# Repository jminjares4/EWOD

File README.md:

# **EWOD** :zap:

## **Description**
This repository hold the hardware designed files for EWOD Senior project. The hardware was developed in KiCAD.

## **Table of Contents**
* [3D](https://github.com/jminjares4/EWOD/tree/main/3D)
  * EWOD step file
* [Hardware](https://github.com/jminjares4/EWOD/tree/main/Hardware)
  * [EWOD KiCad](https://github.com/jminjares4/EWOD/tree/main/Hardware/EWOD%20KiCad)
  * [jlcpcb](https://github.com/jminjares4/EWOD/tree/main/Hardware/jlcpcb)
  * [Readme](https://github.com/jminjares4/EWOD/tree/main/Hardware/README.md)
* [Images](https://github.com/jminjares4/EWOD/tree/main/images)
  * EWOD schematic and printed circuit board (PCB)   
* [Readme](https://github.com/jminjares4/EWOD)

## **Requirements**
- [x] Surface mount SPDT Relays
  - [x] Onboard status LEDs 
- [x] Screw terminals
  - [x] AC Power
  - [x] Step-down transformer 
- [x] SPST Power switch
- [x] External UART to flash ESP32 
- [x] Testpoint
  - [x] 3.3V
  - [x] 5V
  - [x] 16V
  - [x] 164V  

## **EWOD PCB**

## **Development**
| **EWOD** | **Hardware/Software**|
| :--- | :--- |
|**Microcontroller**| |
|**Documentation**| |
| **Electronic Design Automation** ||

## **License**

## **Acknowledgements**
* ECE Department (UTEP)

## **Author**
* [**Jesus Minjares**](https://github.com/jminjares4)<br>
  * **Master of Science in Computer Engineering**<br>

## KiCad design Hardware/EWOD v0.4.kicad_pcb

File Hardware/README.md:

# **EWOD Hardware** :zap:
This directory hold the hardware files for EWOD which was developed in KiCad.

## **Table of Contents**
* **EWOD KiCad**
  * EWOD hardware development was done in KiCad
* **jlcpcb**
  * JLCPCB files for assembly and gerber files

## **Schematic**

## **Top Layer**

## **Bottom Layer**

## **Printed Circuit Board**

## **Author**
* [**Jesus Minjares**](https://github.com/jminjares4)<br>
  * **Master of Science in Computer Engineering**<br>

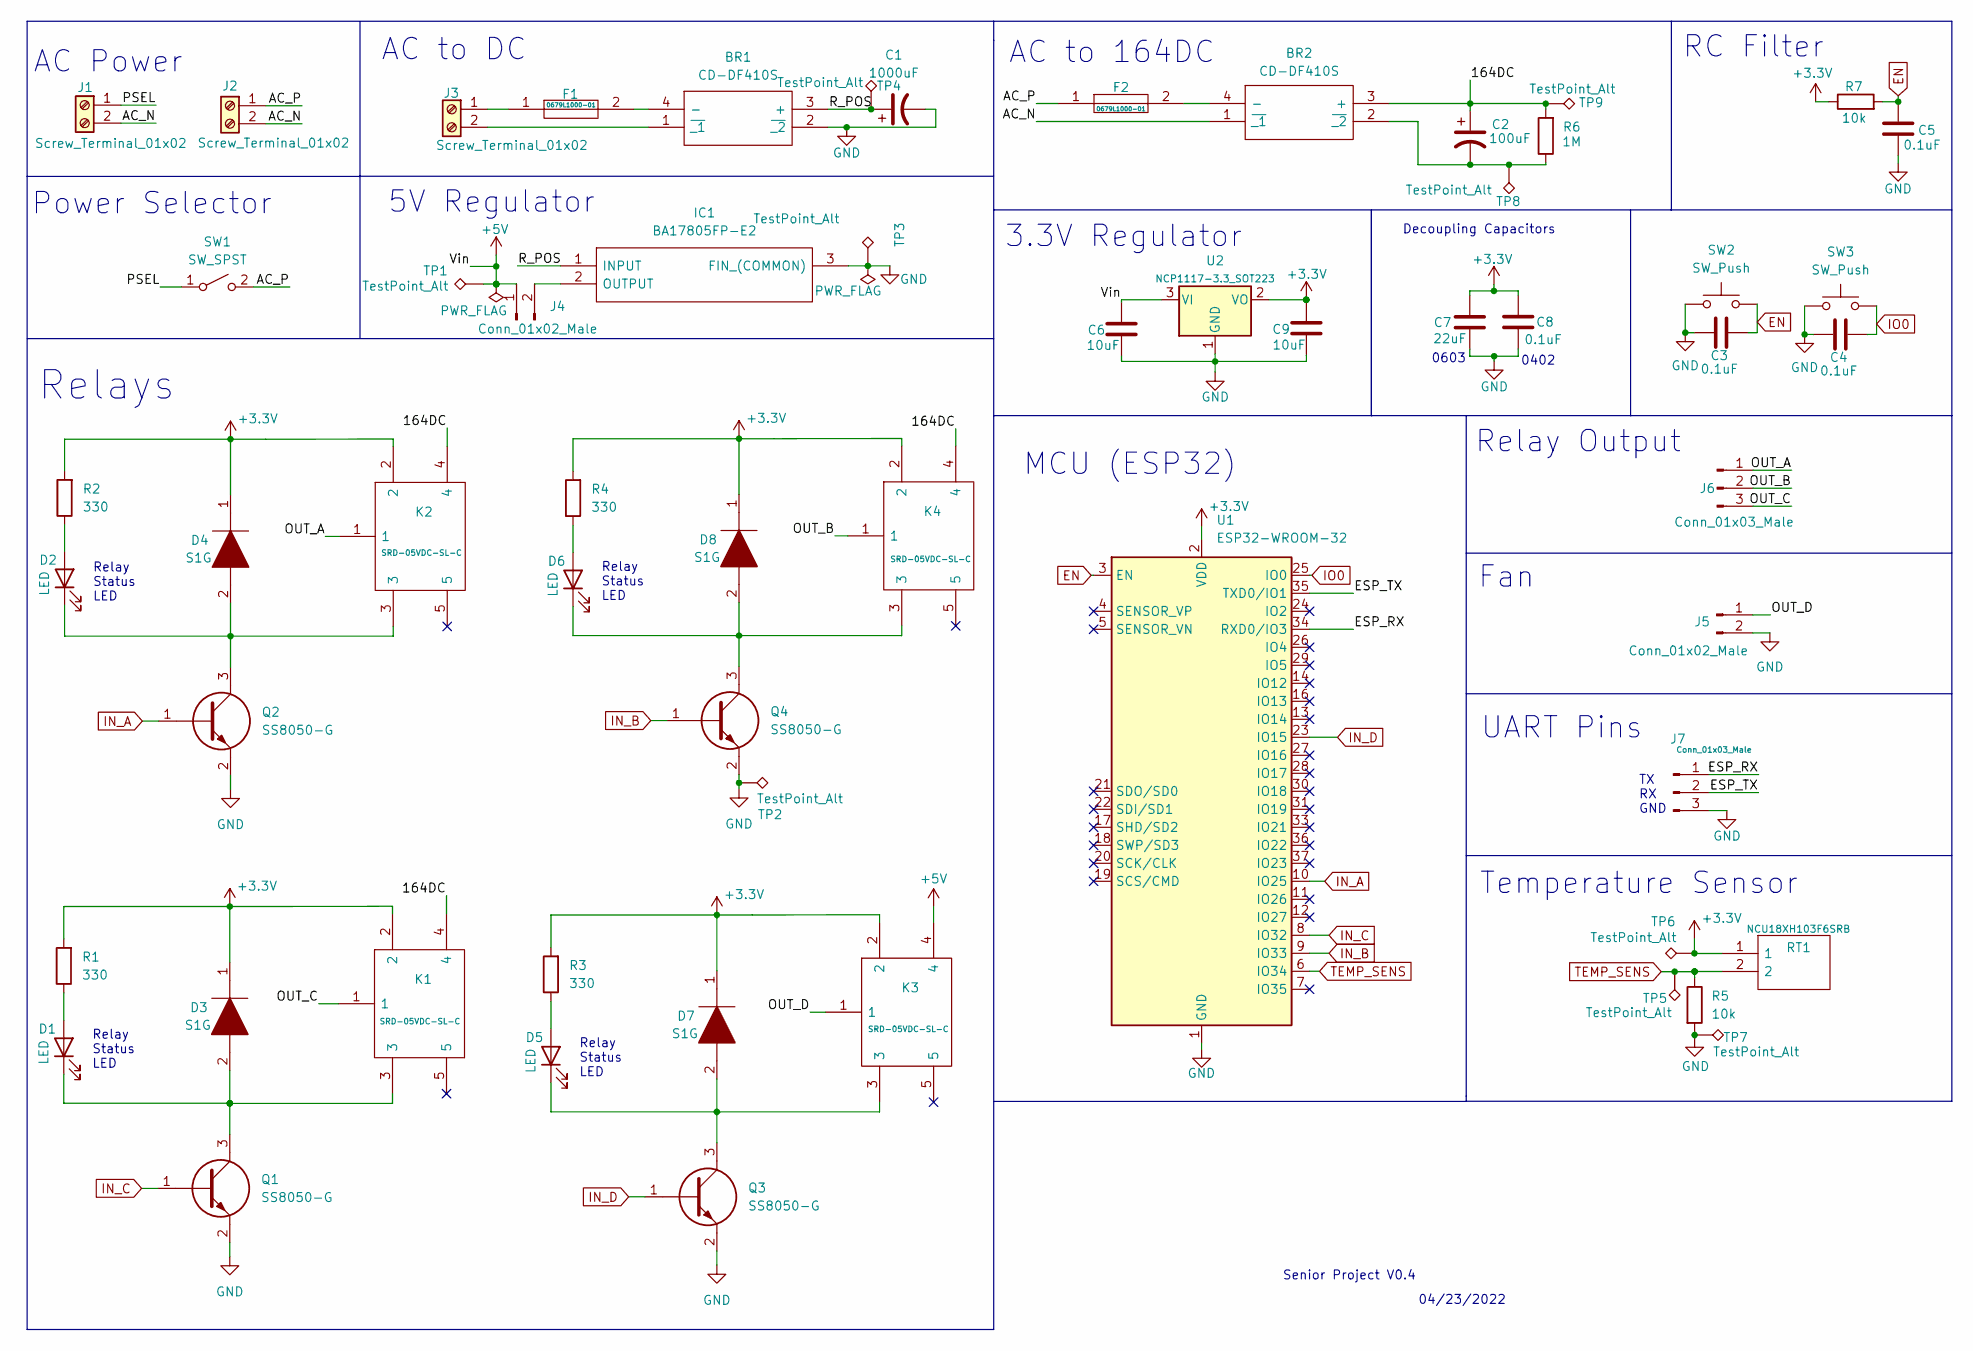
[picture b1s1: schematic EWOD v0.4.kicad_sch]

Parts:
BR1, BR2: CD-DF410S; Manufacturer_Part_Number CD-DF410S; Mouser Part Number 652-CD-DF410S
C1: 1000uF; C_Radial_D10.0mm_H16.0mm_P5.00mm
C2: 100uF; C_Radial_D16.0mm_H25.0mm_P7.50mm
C3, C4, C5, C8: 0.1uF; C_0402_1005Metric
C6, C9: 10uF; C_0603_1608Metric
C7: 22uF; C_0603_1608Metric
D1, D2, D5, D6: LED; LED_0805_2012Metric
D3, D4, D7, D8: S1G; DIOM5227X250N; Manufacturer_Part_Number S1G; Mouser Part Number 512-S1G
F1, F2: 0679L1000-01; FUSC6125X279N; Manufacturer_Part_Number 0679L1000-01
IC1: BA17805FP-E2; ROHM_TO-252-3; Manufacturer_Part_Number BA17805FP-E2; Mouser Part Number 755-BA17805FP-E2
J1, J2, J3: Screw_Terminal_01x02; TerminalBlock_Phoenix_MKDS-1,5-2_1x02_P5.00mm_Horizontal
J4, J5: Conn_01x02_Male; PinHeader_1x02_P2.54mm_Vertical
J6: Conn_01x03_Male; PinHeader_1x03_P2.54mm_Horizontal
J7: Conn_01x03_Male; PinHeader_1x03_P2.54mm_Vertical
K1, K2, K3, K4: SRD-05VDC-SL-C; SRD; Manufacturer_Part_Number SRD-05VDC-SL-C
Q1, Q2, Q3, Q4: SS8050-G; SOT95P240X115-3N; Manufacturer_Part_Number SS8050-G; Mouser Part Number 750-SS8050-G
R1, R2, R3, R4: 330; R_0402_1005Metric
R5, R7: 10k; R_0402_1005Metric
R6: 1M; R_0603_1608Metric
RT1: NCU18XH103F6SRB; THRMC1608X95N; Manufacturer_Part_Number NCU18XH103F6SRB; Mouser Part Number 81-NCU18XH103F6SRB
SW1: SW_SPST; SolderWire-0.75sqmm_1x02_P4.8mm_D1.25mm_OD2.3mm
SW2, SW3: SW_Push; SW_PUSH_6mm
TP1, TP2, TP3, TP4, TP5, TP6, TP7, TP8, TP9: TestPoint_Alt; TestPoint_Pad_1.5x1.5mm
U1: ESP32-WROOM-32
U2: NCP1117-3.3_SOT223; SOT-223-3_TabPin2

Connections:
+3V3: C7.1, C8.1, C9.1, D3.1, D4.1, D7.1, D8.1, K1.2, K2.2, K3.2, K4.2, R1.2, R2.2, R3.2, R4.2, R7.1, RT1.1, TP6.1, U1.2 (VDD), U2.2 (VO)
+5V: C6.1, J4.1, K3.4, TP1.1, U2.3 (VI)
/164DC: BR2.3 (+), C2.1, K1.4, K2.4, K4.4, R6.2, TP9.1
/AC_N: BR2.1 (~_1), J1.2, J2.2
/AC_P: F2.1, J2.1, SW1.2 (B)
/ESP_RX: J7.1, U1.34 (RXD0/IO3)
/ESP_TX: J7.2, U1.35 (TXD0/IO1)
/OUT_A: J6.1, K2.1
/OUT_B: J6.2, K4.1
/OUT_C: J6.3, K1.1
/OUT_D: J5.1, K3.1
/PSEL: J1.1, SW1.1 (A)
/R_POS: BR1.3 (+), C1.1, IC1.1 (INPUT), TP4.1
EN: C3.2, C5.1, R7.2, SW2.2, U1.3 (EN)
GND: BR1.2 (~_2), C1.2, C3.1, C4.1, C5.2, C6.2, C7.2, C8.2, C9.2, IC1.3 (FIN_(COMMON)), J5.2, J7.3, Q1.2, Q2.2, Q3.2, Q4.2, R5.2, SW2.1, SW3.1, TP2.1, TP3.1, TP7.1, U1.1 (GND), U1.15 (GND), U1.38 (GND), U1.39 (GND), U2.1 (GND)
IN_A: Q2.1, U1.10 (IO25)
IN_B: Q4.1, U1.9 (IO33)
IN_C: Q1.1, U1.8 (IO32)
IN_D: Q3.1, U1.23 (IO15)
IO0: C4.2, SW3.2, U1.25 (IO0)
unnamed: BR1.1 (~_1), J3.2
unnamed: BR1.4 (-), F1.2
unnamed: BR2.2 (~_2), C2.2, R6.1, TP8.1
unnamed: BR2.4 (-), F2.2
unnamed: D1.1 (K), D3.2, K1.3, Q1.3
unnamed: D1.2 (A), R1.1
unnamed: D2.1 (K), D4.2, K2.3, Q2.3
unnamed: D2.2 (A), R2.1
unnamed: D5.1 (K), D7.2, K3.3, Q3.3
unnamed: D5.2 (A), R3.1
unnamed: D6.1 (K), D8.2, K4.3, Q4.3
unnamed: D6.2 (A), R4.1
unnamed: F1.1, J3.1
unnamed: IC1.2 (OUTPUT), J4.2
TEMP_SENS: R5.1, RT1.2, TP5.1, U1.6 (IO34)

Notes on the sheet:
Power Selector
AC Power
Fan
Relay Status LED
Relays
04/23/2022
Decoupling Capacitors
0603
RC Filter
Senior Project V0.4
AC to DC
Temperature Sensor
3.3V Regulator
0402
Relay Output
TX RX GND
5V Regulator
UART Pins
MCU (ESP32)
AC to 164DC

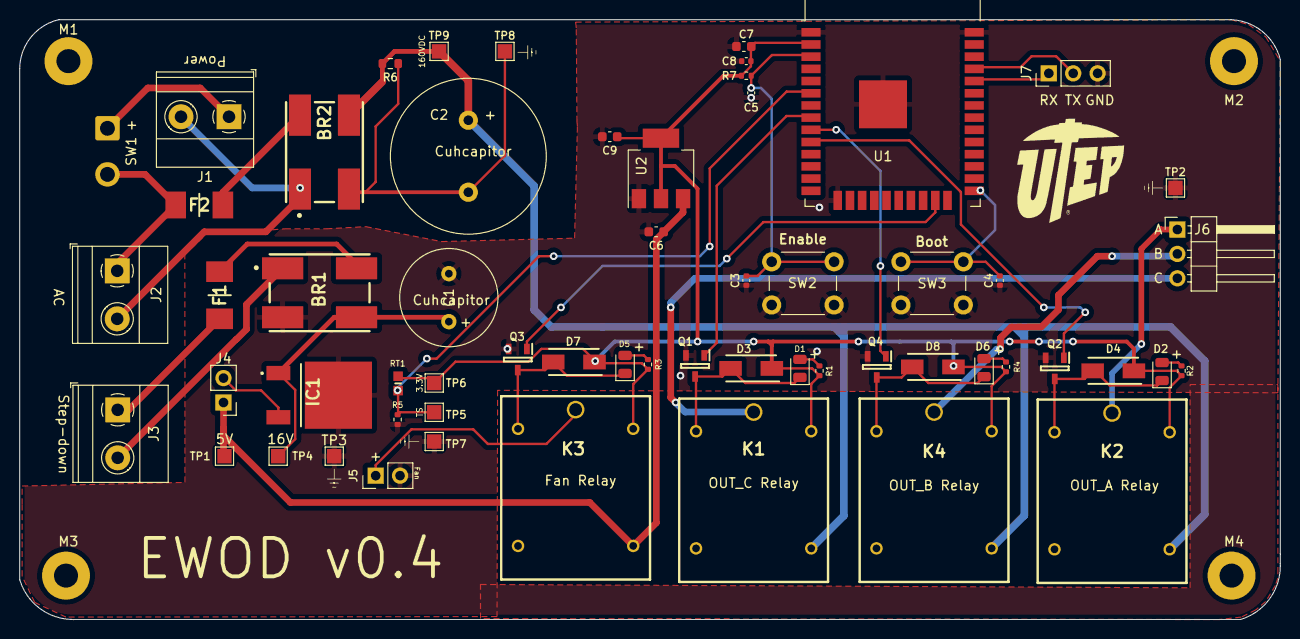
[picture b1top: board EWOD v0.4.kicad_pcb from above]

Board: 2 copper layers, 131.3 x 62.5 mm, 63 parts (0 on the bottom side), 35 nets.

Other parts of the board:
M1, M2, M3, M4: MountingHole_2.5mm_Pad

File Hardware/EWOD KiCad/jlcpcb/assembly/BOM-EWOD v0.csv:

Comment,Designator,Footprint,LCSC
0679L1000-01,F1,FUSC6125X279N,
TestPoint_Alt,TP4,TestPoint_Pad_1.5x1.5mm,
ESP32-WROOM-32,U1,ESP32-WROOM-32,
Screw_Terminal_01x02,J2,"TerminalBlock_Phoenix_MKDS-1,5-2_1x02_P5.00mm_Horizontal",
0.1uF,C3,C_0402_1005Metric,
SW_SPST,SW1,SolderWire-0.75sqmm_1x02_P4.8mm_D1.25mm_OD2.3mm,
330,R1,R_0402_1005Metric,
S1G,D4,DIOM5227X250N,
SRD-05VDC-SL-C,K1,SRD,
SW_Push,SW2,SW_PUSH_6mm,
Screw_Terminal_01x02,J1,"TerminalBlock_Phoenix_MKDS-1,5-2_1x02_P5.00mm_Horizontal",
TestPoint_Alt,TP9,TestPoint_Pad_1.5x1.5mm,
SRD-05VDC-SL-C,K4,SRD,
330,R3,R_0402_1005Metric,
Conn_01x03_Male,J7,PinHeader_1x03_P2.54mm_Vertical,
100uF,C2,C_Radial_D16.0mm_H25.0mm_P7.50mm,
NCU18XH103F6SRB,RT1,THRMC1608X95N,
Screw_Terminal_01x02,J3,"TerminalBlock_Phoenix_MKDS-1,5-2_1x02_P5.00mm_Horizontal",
TestPoint_Alt,TP3,TestPoint_Pad_1.5x1.5mm,
LED,D2,LED_0805_2012Metric,
1M,R6,R_0603_1608Metric,
S1G,D3,DIOM5227X250N,
TestPoint_Alt,TP2,TestPoint_Pad_1.5x1.5mm,
330,R2,R_0402_1005Metric,
CD-DF410S,BR2,CD-DF410S,
SS8050-G,Q3,SOT95P240X115-3N,
TestPoint_Alt,TP8,TestPoint_Pad_1.5x1.5mm,
TestPoint_Alt,TP1,TestPoint_Pad_1.5x1.5mm,
LED,D6,LED_0805_2012Metric,
NCP1117-3.3_SOT223,U2,SOT-223-3_TabPin2,
SRD-05VDC-SL-C,K3,SRD,
10k,R5,R_0402_1005Metric,
SS8050-G,Q2,SOT95P240X115-3N,
SRD-05VDC-SL-C,K2,SRD,
10uF,C6,C_0603_1608Metric,
Conn_01x02_Male,J4,PinHeader_1x02_P2.54mm_Vertical,
TestPoint_Alt,TP6,TestPoint_Pad_1.5x1.5mm,
0.1uF,C5,C_0402_1005Metric,
S1G,D7,DIOM5227X250N,
CD-DF410S,BR1,CD-DF410S,
BA17805FP-E2,IC1,ROHM_TO-252-3,
10uF,C9,C_0603_1608Metric,
LED,D1,LED_0805_2012Metric,
22uF,C7,C_0603_1608Metric,
10k,R7,R_0402_1005Metric,
Conn_01x02_Male,J5,PinHeader_1x02_P2.54mm_Vertical,
0.1uF,C4,C_0402_1005Metric,
0.1uF,C8,C_0402_1005Metric,
1000uF,C1,C_Radial_D10.0mm_H16.0mm_P5.00mm,
330,R4,R_0402_1005Metric,
TestPoint_Alt,TP5,TestPoint_Pad_1.5x1.5mm,
Conn_01x03_Male,J6,PinHeader_1x03_P2.54mm_Horizontal,
TestPoint_Alt,TP7,TestPoint_Pad_1.5x1.5mm,
SS8050-G,Q4,SOT95P240X115-3N,
SS8050-G,Q1,SOT95P240X115-3N,
S1G,D8,DIOM5227X250N,
LED,D5,LED_0805_2012Metric,
SW_Push,SW3,SW_PUSH_6mm,
0679L1000-01,F2,FUSC6125X279N,

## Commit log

2022-04-24 Add gitignore to repo
2022-04-24 Added EWOD v0.4 hardware development
2022-04-24 Moved everything to subdirectory
2022-04-24 Updated hardware repo
2022-04-24 Added EWOD latest images
2022-04-24 Added readme for hardware section
2022-04-24 Updated EWOD
2022-04-24 Updated gif
2022-04-24 First commit for firmware
2022-04-24 Update readme and added license
2022-04-25 Updated readme with only hardware files
2022-04-25 remove firmware

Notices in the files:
README.md:
[License: GPL v3](https://www.gnu.org/licenses/gpl-3.0)
